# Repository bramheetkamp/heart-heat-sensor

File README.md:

# Pulse — Heart Rate + Core Temperature Wearable Companion

A consumer-grade iOS app and sync backend for a BLE wearable with a MAX30102 heart-rate sensor and dual temperature sensing, built on an nRF52840 DK running Nordic's `ble_app_hrs` firmware.

The hardware doesn't exist yet — everything works end-to-end against simulated data via **Demo Mode** so you can develop and demo now, then swap in the real device later.

---

## Branching

- **`develop`** is the **default / working branch** — branch your features off it and open PRs into it.
- **`main`** is the release branch (production-ready history).
- `develop` is protected: it can't be deleted or force-pushed. Day-to-day work happens on `develop`; merge into `main` for releases.

---

## Project layout

```
heart-heat-sensor/
├── ios/          iOS app (Swift + SwiftUI + CoreBluetooth)
└── backend/      Sync API (Node.js + TypeScript + Fastify + SQLite)
```

---

## 1. Running the backend

### Prerequisites
- Node.js ≥ 20
- (Optional) Docker + Docker Compose

### Quick start (Node.js)

```bash
cd backend
npm install
cp .env.example .env          # edit JWT_SECRET at minimum
npm run dev                   # starts on http://localhost:3100
```

### Quick start (Docker)

```bash
cd backend
docker-compose up
```

### Seed the database with demo data

```bash
npm run seed
```

This creates a test account (`test@example.com` / `password123`) preloaded with 35 days of readings across four scenarios and fires the warnings engine:

| Days    | Scenario                                    | Warnings fired          |
|---------|---------------------------------------------|-------------------------|
| 1–28    | Normal week with workouts and sleep         | None                    |
| 29–31   | Getting sick — creeping HR + temp baseline  | `GETTING_SICK`          |
| 32–33   | Overheating workout — temp spike to 39.1 °C | `OVERHEATING`           |
| 34–35   | Poor recovery — elevated HR, low HRV        | `FATIGUE_RECOVERY`      |

### Running backend tests

```bash
npm test
# 50 tests, all in-process via Fastify inject() — no port required
```

### API overview

| Method | Path | Auth | Description |
|--------|------|------|-------------|
| POST | `/auth/register` | — | Email + password registration |
| POST | `/auth/login` | — | Returns JWT |
| POST | `/auth/apple` | — | Sign in with Apple |
| POST | `/readings/batch` | JWT | Upload reading batch |
| GET  | `/readings` | JWT | Fetch history (`from`, `to`, `limit` params) |
| GET  | `/warnings` | JWT | Fetch user's warnings |
| GET  | `/warnings/:id` | JWT | Single warning detail |
| POST | `/warnings/recompute` | JWT | Re-run warnings engine |
| GET  | `/.well-known/apple-app-site-association` | — | Universal Links config |
| GET  | `/health` | — | Health check |

---

## 2. Running the iOS app

### Prerequisites

- macOS with **Xcode 15+** (iOS 17 SDK)
- [XcodeGen](https://github.com/yonaskolb/XcodeGen) (install via `brew install xcodegen`)

### Generate the Xcode project

```bash
cd ios
bash generate_project.sh    # installs XcodeGen if missing, then generates HeartRate.xcodeproj
open HeartRate.xcodeproj
```

Select any iPhone 17 Simulator and press **⌘R** to run.

> **Team ID**: open `project.yml`, find `DEVELOPMENT_TEAM: ""` and set your Apple Developer Team ID if you want to run on a physical device.

### Running iOS unit tests

```bash
cd ios
xcodebuild test \
  -project HeartRate.xcodeproj \
  -scheme HeartRate \
  -destination 'platform=iOS Simulator,name=iPhone 16' \
  2>&1 | xcpretty
```

Tests cover:
- `HRMeasurementParserTests` — HR characteristic byte parsing (8-bit, 16-bit, RR intervals, energy expended, sensor contact)
- `TemperatureMeasurementParserTests` — IEEE-11073 float decoding, Fahrenheit conversion, site hints
- `WarningsEngineTests` — all three warning rules, baseline computation, RMSSD calculation

---

## 3. Demo Mode

Demo Mode feeds **simulated data through the same BLE pipeline** as a real device — the UI, parsers, and warnings engine see no difference.

### Enabling Demo Mode

- **First launch**: tap *"I don't have my device yet — use demo mode"* during onboarding pairing step
- **Any time**: Settings → Demo Mode toggle
- The mode persists in `UserDefaults` key `isDemoMode`

### Scenario presets

| Scenario | What it simulates |
|----------|-------------------|
| **Normal Week** | Typical HR 55–75 bpm, core 36.4–36.8 °C, circadian rhythm, workouts |
| **Overheating Workout** | Core temp spike to 39.1 °C during an active session → fires `OVERHEATING` |
| **Getting Sick (3 days)** | Resting HR creeps up +3 bpm/day, core temp +0.15 °C/day → fires `GETTING_SICK` |
| **Poor Recovery** | Elevated resting HR + very regular RR intervals (near-zero HRV) → fires `FATIGUE_RECOVERY` |

Switch scenarios in **Settings → Demo Scenario** or via the wand button on the Dashboard. Switching seeds fresh readings and immediately re-runs the warnings engine.

---

## 4. Deep links

### Custom URL scheme (`heartrate://`)

| URL | Navigates to |
|-----|-------------|
| `heartrate://dashboard` | Dashboard |
| `heartrate://history/hr` | HR history chart |
| `heartrate://history/core` | Core temp chart |
| `heartrate://history/hrv` | HRV chart |
| `heartrate://warnings/<uuid>` | Warning detail |
| `heartrate://settings` | Settings |
| `heartrate://pair` | Device pairing |

### Testing in Simulator

```bash
# Open a deep link in the booted Simulator
xcrun simctl openurl booted "heartrate://dashboard"
xcrun simctl openurl booted "heartrate://warnings/123e4567-e89b-12d3-a456-426614174000"
xcrun simctl openurl booted "heartrate://history/core"
```

### Universal Links

The backend serves `/.well-known/apple-app-site-association`. To enable Universal Links in production:

1. Deploy the backend to `yourdomain.com` over HTTPS.
2. Edit `ios/HeartRate/HeartRate.entitlements` — replace `yourdomain.com` with your actual domain.
3. Set `APPLE_TEAM_ID` env var on the backend so the AASA file contains your real team ID.
4. Universal Links then work as `https://yourdomain.com/warnings/<id>` etc.

---

## 5. Testing BLE with a simulated peripheral (LightBlue)

If you have an iPhone/iPad with [LightBlue](https://punchthrough.com/lightblue/), you can advertise a fake HR sensor:

1. Open LightBlue → **Create Virtual Device**
2. Add service `180D` (Heart Rate)
3. Add characteristic `2A37` (HR Measurement)
   - Value example (72 bpm, no RR): `0x00 0x48`
   - Value example (65 bpm, two RR intervals): `0x10 0x41 0xAA 0x03 0xB8 0x03`
4. Set it to notify
5. Run the iOS app in Simulator on the **same Mac** (BLE works between phone and Simulator via the Mac's Bluetooth adapter)

For temperature, add service `1809`, characteristic `2A1C`:
- Example (36.7 °C): `0x00 0x6F 0x01 0x00 0xFF`

---

## 6. Wiring the iOS app to the real device

When the nRF52840 DK is ready:

1. Turn off Demo Mode in Settings
2. The app scans for peripherals advertising `0x180D` (Heart Rate Service)
3. On connect, it discovers and subscribes to `0x2A37` (HR) and `0x2A1C` (Temperature)
4. A second temperature characteristic on the same service is automatically detected and labelled "Site 2"

The firmware only needs to implement standard GATT: HR Measurement notify + Temperature Measurement notify.

---

## Architecture notes

### iOS

```
BLE Layer ──► BLEService ──► Parsers ──► DataStore (SwiftData)
                                              │
                                              ▼
                                       WarningsEngine
                                              │
                                              ▼
                                     Views / Dashboard
```

- **BLETransportProtocol** makes `CoreBluetoothTransport` and `MockBLETransport` interchangeable
- **WarningsEngine** is a pure struct with static methods — fully unit testable, no SwiftData dependency
- **AppRouter** uses `NavigationPath` + typed `AppRoute` enum — every screen is deep-linkable
- **SwiftData** persistence, **Swift Charts** for all trend charts
- Sync is additive and optional — the app works 100% offline

### Backend

- **Fastify** + **better-sqlite3** — fast to start, single binary for local dev
- **JWT** authentication, bcrypt password hashing
- Warnings engine runs server-side as a recompute operation; client engine handles offline/realtime
- SQLite WAL mode for concurrent reads during sync

### Extension point — Garmin Health API

The `SyncService.swift` contains a clearly marked stub:

```swift
// MARK: - Future: Garmin Health API Integration
// func syncGarminData(token: String) async throws { fatalError("Not implemented") }
```

On the backend, add a `/integrations/garmin` route group when ready.

---

## Environment variables (backend)

| Variable | Default | Description |
|----------|---------|-------------|
| `PORT` | `3100` | HTTP port |
| `JWT_SECRET` | `dev_secret_change_me` | **Change in production** |
| `DATABASE_PATH` | `./data/heartrate.db` | SQLite file path |
| `APPLE_CLIENT_ID` | `com.pulse.app` | Bundle ID checked against `aud` in Apple identity tokens |
| `APPLE_BUNDLE_ID` | `com.heartrate.app` | Bundle ID embedded in the AASA file |
| `APPLE_TEAM_ID` | `XXXXXXXXXX` | Apple Developer Team ID embedded in the AASA file |
| `API_BASE_URL` | `http://localhost:3100` | Set as Xcode env var to point the iOS app at staging |

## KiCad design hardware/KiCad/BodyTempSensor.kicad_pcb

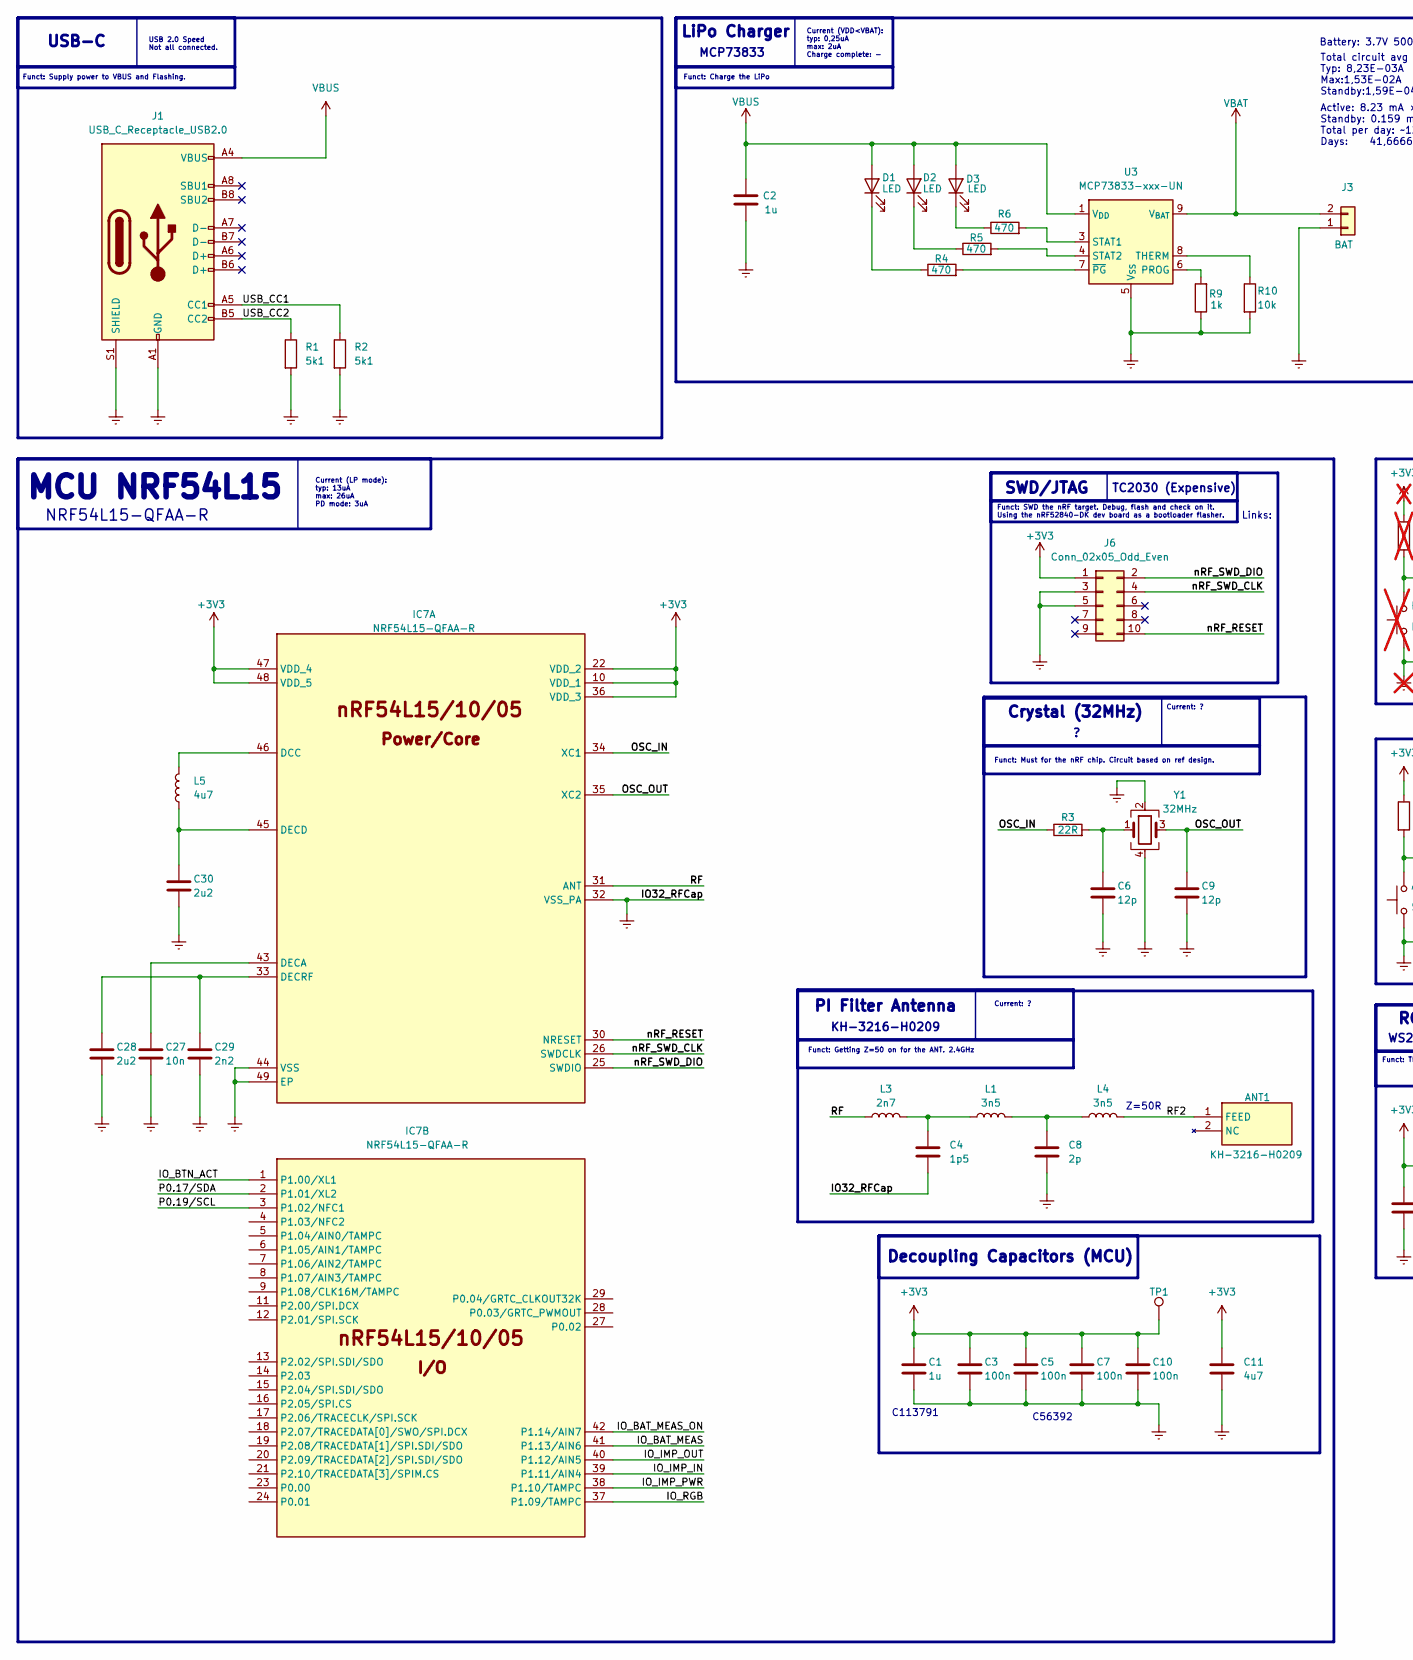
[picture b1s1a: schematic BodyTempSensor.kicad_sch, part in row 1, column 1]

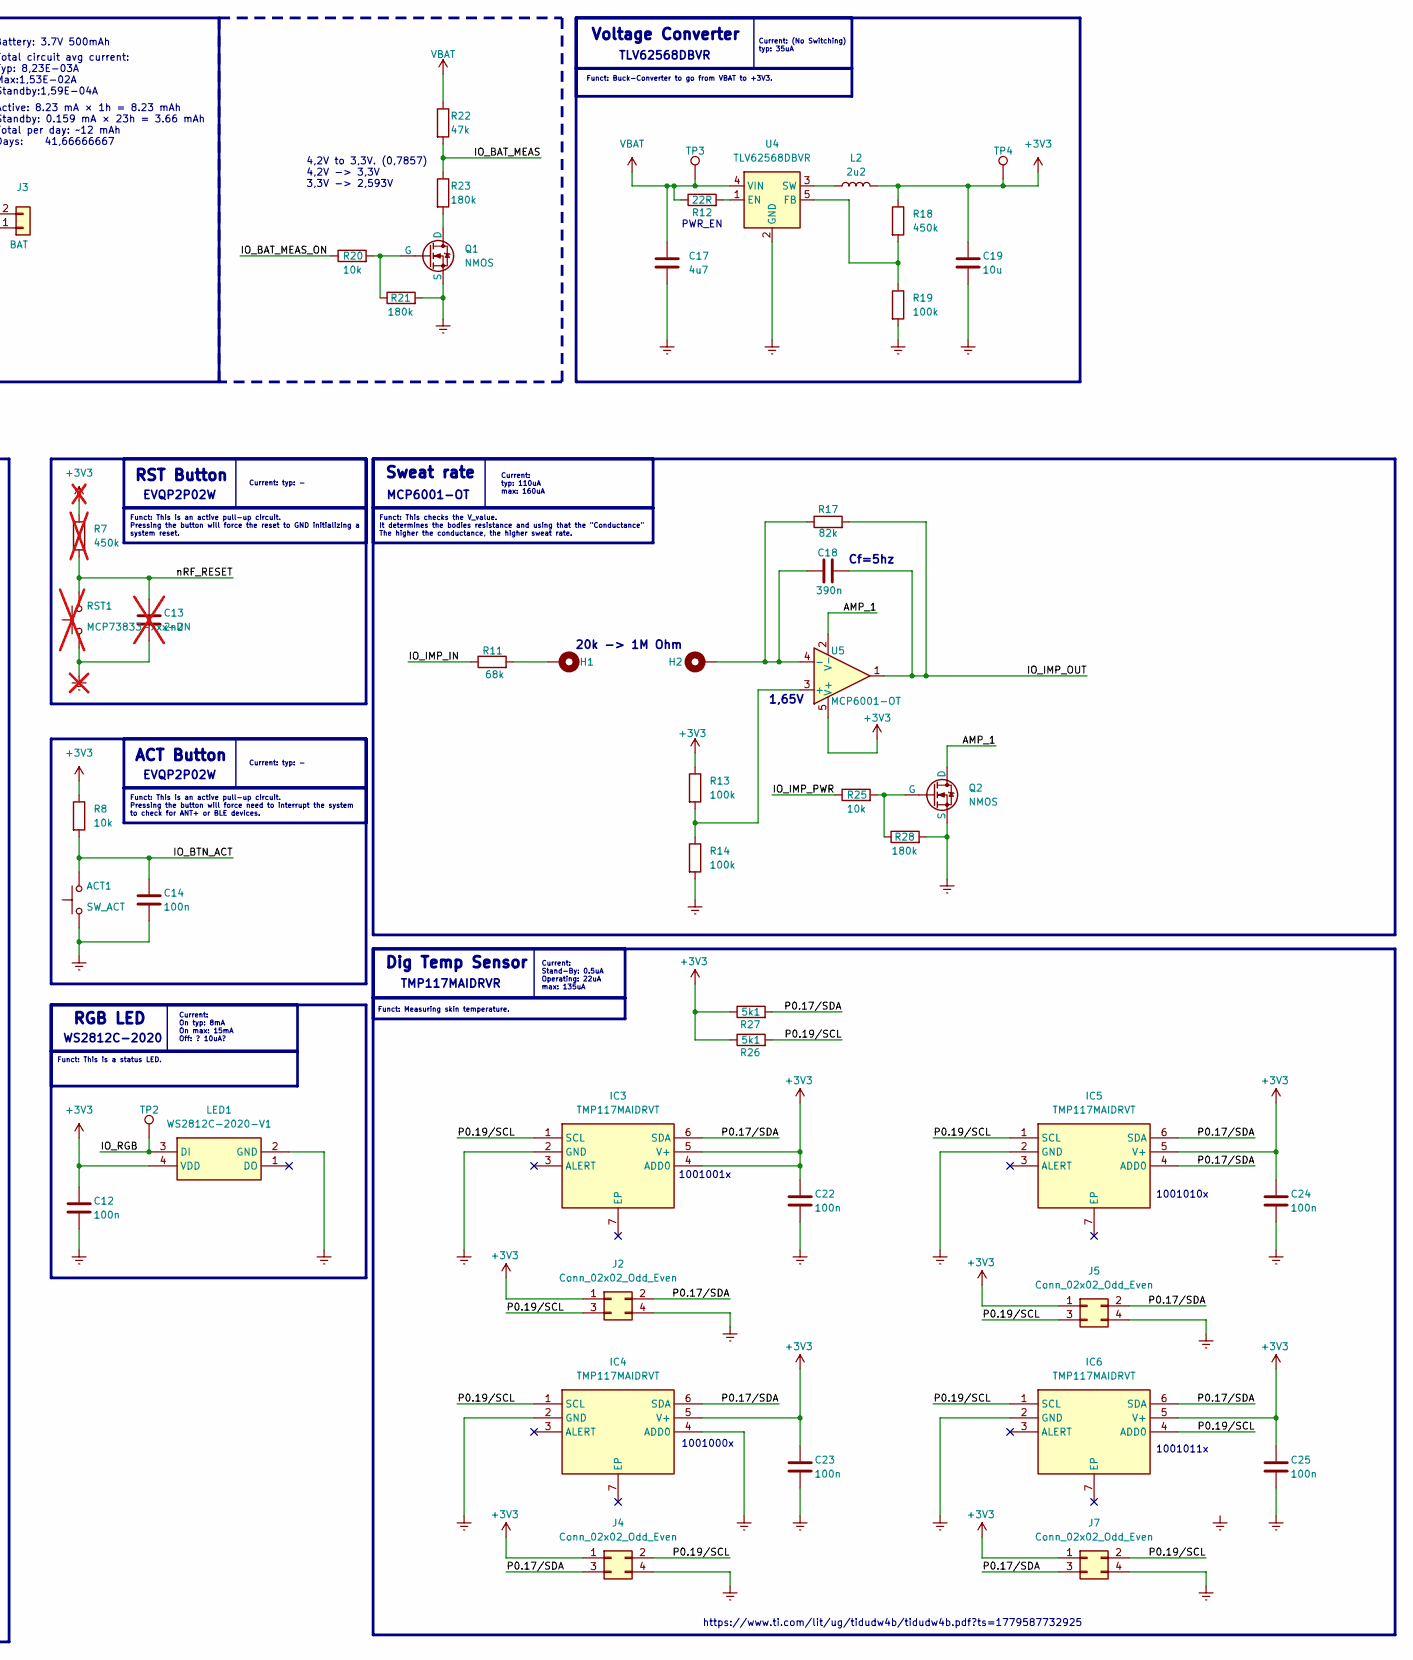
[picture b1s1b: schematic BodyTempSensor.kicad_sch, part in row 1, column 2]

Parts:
ACT1: SW_ACT; SW_SPST_EVQP2; Manufacturer_Part_Number EVQP2P02W; LCSC PART # C512395
ANT1: KH-3216-H0209; ANTC3216X140N; Manufacturer_Part_Number KH-3216-H0209; LCSC PART # C2925417
C1: 1u; C_0402_1005Metric_Pad0.74x0.62mm_HandSolder; Manufacturer_Part_Number CC0402MRX5R6BB105; LCSC PART # C113791
C2: 1u; C_0402_1005Metric_Pad0.74x0.62mm_HandSolder; Manufacturer_Part_Number CC0402KRX5R6BB105; LCSC PART # C106254
C3, C5, C7, C10, C12, C14, C22, C23, C24, C25: 100n; C_0402_1005Metric_Pad0.74x0.62mm_HandSolder; Manufacturer_Part_Number C1005X5R1E104KT000E; LCSC PART # C361203
C4: 1p5; C_0402_1005Metric_Pad0.74x0.62mm_HandSolder; LCSC PART # TBT
C6, C9: 12p; C_0402_1005Metric_Pad0.74x0.62mm_HandSolder; Manufacturer_Part_Number CC0402JRNPO9BN120; LCSC PART # C106201
C8: 2p; C_0402_1005Metric_Pad0.74x0.62mm_HandSolder; Manufacturer_Part_Number CC0402BRNPO9BN2R0; LCSC PART # CC0402BRNPO9BN2R0
C11, C17: 4u7; C_0402_1005Metric_Pad0.74x0.62mm_HandSolder; Manufacturer_Part_Number GRM155R60J475ME47D; LCSC PART # C82453
C13: 2n2; C_0402_1005Metric_Pad0.74x0.62mm_HandSolder; Manufacturer_Part_Number CC0402KRX7R9BB222; LCSC PART # C106861; not fitted
C18: 390n; C_0402_1005Metric_Pad0.74x0.62mm_HandSolder; Manufacturer_Part_Number TCC0402X5R394K160AT; LCSC PART # C7393858
C19: 10u; C_0402_1005Metric_Pad0.74x0.62mm_HandSolder; Manufacturer_Part_Number 0402X106M100CT; LCSC PART # C2992625
C27: 10n; C_0402_1005Metric_Pad0.74x0.62mm_HandSolder; Manufacturer_Part_Number CC0402KRX7R8BB103; LCSC PART # C327025
C28, C30: 2u2; C_0402_1005Metric_Pad0.74x0.62mm_HandSolder; Manufacturer_Part_Number 0402X225K100CT; LCSC PART # C295941
C29: 2n2; C_0402_1005Metric_Pad0.74x0.62mm_HandSolder; Manufacturer_Part_Number CC0402KRX7R9BB222; LCSC PART # C106861
D1, D2, D3: LED; LED_0402_1005Metric_Pad0.77x0.64mm_HandSolder; Manufacturer_Part_Number XL-1005SURC; LCSC PART # C965790
H1, H2: (no value)
IC3, IC4, IC5, IC6: TMP117MAIDRVT; SON65P200X200X80-7N; Manufacturer_Part_Number TMP117MAIDRVR; Mouser Part Number 595-TMP117MAIDRVT
IC7: NRF54L15-QFAA-R; QFN40P600X600X95-49N; Manufacturer_Part_Number NRF54L15-QFAA-R; Mouser Part Number 949-NRF54L15-QFAA-R
J1: USB_C_Receptacle_USB2.0; USB_C_Receptacle_GCT_USB4105-xx-A_16P_TopMnt_Horizontal; Manufacturer_Part_Number TYPE-C-31-M-14; LCSC PART # C223907
J2, J5: Conn_02x02_Odd_Even; PinHeader_2x02_P1.27mm_Vertical_SMD
J3: BAT; JST_PH_B2B-PH-K_1x02_P2.00mm_Vertical
J4, J7: Conn_02x02_Odd_Even; PinHeader_2x02_P1.27mm_Vertical
J6: Conn_02x05_Odd_Even; PinHeader_2x05_P1.27mm_Vertical
L1, L4: 3n5; L_0201_0603Metric_Pad0.64x0.40mm_HandSolder; Manufacturer_Part_Number TCGL0603C3N5SZT; LCSC PART # C52109755
L2: 2u2; L_Wurth_WE-LQSH-4020; Manufacturer_Part_Number SMNR4020-2.2UH; LCSC PART # C135262
L3: 2n7; L_0402_1005Metric_Pad0.77x0.64mm_HandSolder; Manufacturer_Part_Number LQG15HS2N7S02D; LCSC PART # C77108
L5: 4u7; L_0603_1608Metric_Pad1.05x0.95mm_HandSolder; Manufacturer_Part_Number MLZ1608M4R7WT000; LCSC PART # C76799
LED1: WS2812C-2020-V1; WS2812C2020; Manufacturer_Part_Number WS2812C-2020; LCSC PART # C2976072
Q1, Q2: NMOS; SOT-23; Manufacturer_Part_Number AO3400A; LCSC PART # C20917
R1, R2, R26, R27: 5k1; R_0402_1005Metric_Pad0.72x0.64mm_HandSolder; Manufacturer_Part_Number RC0402JR-075K1L; LCSC PART # C105873
R3, R12: 22R; R_0402_1005Metric_Pad0.72x0.64mm_HandSolder; Manufacturer_Part_Number ERJ2RKF22R0X; LCSC PART # C413049
R4, R5, R6: 470; R_0402_1005Metric_Pad0.72x0.64mm_HandSolder; Manufacturer_Part_Number SCR0603J470R; LCSC PART # C3017744
R7: 450k; R_0402_1005Metric_Pad0.72x0.64mm_HandSolder; Manufacturer_Part_Number FRC0402F4503TS; LCSC PART # C5159688; not fitted
R8, R10, R20, R25: 10k; R_0402_1005Metric_Pad0.72x0.64mm_HandSolder; Manufacturer_Part_Number WR04X1002FTL; LCSC PART # C163810
R9: 1k; R_0402_1005Metric_Pad0.72x0.64mm_HandSolder; Manufacturer_Part_Number RC0402FR-071KL; LCSC PART # C106235
R11: 68k; R_0402_1005Metric_Pad0.72x0.64mm_HandSolder; Manufacturer_Part_Number RC0402FR-0768KL; LCSC PART # C238338
R13, R14, R19: 100k; R_0402_1005Metric_Pad0.72x0.64mm_HandSolder; Manufacturer_Part_Number RT0402CRE07100KL; LCSC PART # C705662
R17: 82k; R_0402_1005Metric_Pad0.72x0.64mm_HandSolder; Manufacturer_Part_Number RC0402FR-0782KL; LCSC PART # C137932
R18: 450k; R_0402_1005Metric_Pad0.72x0.64mm_HandSolder; Manufacturer_Part_Number FRC0402F4503TS; LCSC PART # C5159688
R21, R23, R28: 180k; R_0402_1005Metric_Pad0.72x0.64mm_HandSolder; Manufacturer_Part_Number RC0402FR-07180KL; LCSC PART # C138046
R22: 47k; R_0402_1005Metric_Pad0.72x0.64mm_HandSolder; Manufacturer_Part_Number RC0402FR-0747KL; LCSC PART # C93943
RST1: MCP73833-xxx-UN; MSOP-10_3x3mm_P0.5mm; Manufacturer_Part_Number MCP73831T-2ACI/OT; LCSC PART # C424093; not fitted
TP1, TP2, TP3, TP4: TestPoint; TestPoint_Pad_D1.0mm
U3: MCP73833-xxx-UN; MSOP-10_3x3mm_P0.5mm; Manufacturer_Part_Number MCP73831T-2ACI/OT; LCSC PART # C424093
U4: TLV62568DBVR; SOT-23-5; Manufacturer_Part_Number TLV62568DBVR; LCSC PART # C163219
U5: MCP6001-OT; SOT-23-5; Manufacturer_Part_Number MCP6001T-I/OT; LCSC PART # C116490
Y1: 32MHz; Crystal_SMD_3225-4Pin_3.2x2.5mm; Manufacturer_Part_Number X322532MMB4SI; LCSC PART # C113671

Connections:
+3V3: C1.1, C3.1, C5.1, C7.1, C10.1, C11.1, C12.1, C19.1, C22.1, C23.1, C24.1, C25.1, IC3.4 (ADD0), IC3.5 (V+), IC4.5 (V+), IC5.5 (V+), IC6.5 (V+), IC7.10 (VDD_1), IC7.22 (VDD_2), IC7.36 (VDD_3), IC7.47 (VDD_4), IC7.48 (VDD_5), J2.1, J4.1, J5.1, J6.1, J7.1, L2.2, LED1.4 (VDD), R7.1, R8.1, R13.1, R18.1, R26.1, R27.1, TP1.1 (1_1), TP4.1 (1_1), U5.5 (V+)
/AMP_1: Q2.1 (D), U5.2 (V-)
/IO_BAT_MEAS: IC7.41 (P1.13/AIN6), R22.2, R23.1
/IO_BAT_MEAS_ON: IC7.42 (P1.14/AIN7), R20.1
/IO_BTN_ACT: ACT1.2, C14.1, IC7.1 (P1.00/XL1), R8.2
/IO_IMP_IN: IC7.39 (P1.11/AIN4), R11.1
/IO_IMP_OUT: C18.2, IC7.40 (P1.12/AIN5), R17.2, U5.1
/IO_IMP_PWR: IC7.38 (P1.10/TAMPC), R25.1
/IO_RGB: IC7.37 (P1.09/TAMPC), LED1.3 (DI), TP2.1 (1_1)
/OSC_IN: IC7.34 (XC1), R3.1
/OSC_OUT: C9.1, IC7.35 (XC2), Y1.3
/P0.17/SDA: IC3.6 (SDA), IC4.6 (SDA), IC5.4 (ADD0), IC5.6 (SDA), IC6.6 (SDA), IC7.2 (P1.01/XL2), J2.2, J4.3, J5.2, J7.3, R27.2
/P0.19/SCL: IC3.1 (SCL), IC4.1 (SCL), IC5.1 (SCL), IC6.1 (SCL), IC6.4 (ADD0), IC7.3 (P1.02/NFC1), J2.3, J4.2, J5.3, J7.2, R26.2
/RF: IC7.31 (ANT), L3.1
/RF2: ANT1.1 (FEED_1), L4.2
/USB_CC1: J1.A5 (CC1), R2.1
/USB_CC2: J1.B5 (CC2), R1.1
/nRF_RESET: C13.1, IC7.30 (NRESET), J6.10, R7.2, RST1.2
/nRF_SWD_CLK: IC7.26 (SWDCLK), J6.4
/nRF_SWD_DIO: IC7.25 (SWDIO), J6.2
Earth: ACT1.1, C1.2, C2.1, C3.2, C4.2, C5.2, C6.2, C7.2, C8.2, C9.2, C10.2, C11.2, C12.2, C13.2, C14.2, C17.2, C19.2, C22.2, C23.2, C24.2, C25.2, C27.2, C28.2, C29.2, C30.2, IC3.2 (GND), IC4.2 (GND), IC4.4 (ADD0), IC5.2 (GND), IC6.2 (GND), IC7.32 (VSS_PA), IC7.44 (VSS), IC7.49 (EP), J1.A1 (GND), J1.A12 (GND), J1.B1 (GND), J1.B12 (GND), J1.S1 (SHIELD), J2.4, J3.1, J4.4, J5.4, J6.3, J6.5, J7.4, LED1.2 (GND), Q1.3 (S), Q2.3 (S), R1.2, R2.2, R9.1, R10.2, R14.2, R19.2, R21.2, R28.2, RST1.1, U3.5 (V_{SS}), U4.2 (GND), Y1.2, Y1.4
unnamed: C4.1, L1.1, L3.2
unnamed: C6.1, R3.2, Y1.1
unnamed: C8.1, L1.2, L4.1
unnamed: D1.1 (K), R4.1
unnamed: D2.1 (K), R5.1
unnamed: D3.1 (K), R6.1
unnamed: H1.1 (1_1), R11.2
unnamed: IC7.46 (DCC), L5.2
unnamed: C27.1, IC7.43 (DECA)
unnamed: C30.1, IC7.45 (DECD), L5.1
unnamed: C28.1, C29.1, IC7.33 (DECRF)
unnamed: Q1.1 (D), R23.2
unnamed: Q1.2 (G), R20.2, R21.1
unnamed: Q2.2 (G), R25.2, R28.1
unnamed: R9.2, U3.6 (PROG)
unnamed: R6.2, U3.3 (STAT1)
unnamed: R5.2, U3.4 (STAT2)
unnamed: R10.1, U3.8 (THERM)
unnamed: R4.2, U3.7 (~PG)
unnamed: R12.2, U4.1 (EN)
unnamed: R18.2, R19.1, U4.5 (FB)
unnamed: L2.1, U4.3 (SW)
unnamed: R13.2, R14.1, U5.3 (+)
unnamed: C18.1, H2.1 (1_1), R17.1, U5.4 (-)
VBAT: C17.1, J3.2, R12.1, R22.1, TP3.1 (1_1), U3.9 (V_{BAT}), U3.10 (V_{BAT}), U4.4 (VIN)
VBUS: C2.2, D1.2 (A), D2.2 (A), D3.2 (A), J1.A4 (VBUS), J1.A9 (VBUS), J1.B4 (VBUS), J1.B9 (VBUS), U3.1 (V_{DD}), U3.2 (V_{DD})

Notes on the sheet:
https://www.ti.com/lit/ug/tidudw4b/tidudw4b.pdf?ts=1779587732925
NRF54L15-QFAA-R
EVQP2P02W
Funct: Must for the nRF chip. Circuit based on ref design.
Crystal (32MHz)
Funct: Supply power to VBUS and Flashing.
MCP73833
Current: ?
Funct: Measuring skin temperature.
Active: 8.23 mA × 1h = 8.23 mAh Standby: 0.159 mA × 23h = 3.66 mAh Total per day: ~12 mAh Days: 41,66666667
Funct: Buck-Converter to go from VBAT to +3V3.
1,65V
Current: typ: -
Sweat rate
TLV62568DBVR
RGB LED
MCP6001-OT
Current (LP mode): typ: 13uA max: 26uA PD mode: 3uA
Current: typ: 110uA max: 160uA
Current (VDD<VBAT): typ: 0,25uA max: 2uA Charge complete: -
20k -> 1M Ohm
Funct: This is an active pull-up circuit. Pressing the button will force need to interrupt the system to check for ANT+ or BLE devices.
Z=50R
C113791
TMP117MAIDRVR
C56392
Funct: SWD the nRF target. Debug, flash and check on it. Using the nRF52840-DK dev board as a bootloader flasher.
Battery: 3.7V 500mAh
Funct: Getting Z=50 on for the ANT. 2.4GHz
Funct: This is a status LED.
Voltage Converter
ACT Button
PI Filter Antenna
Current: On typ: 8mA On max: 15mA Off: ? 10uA?
LiPo Charger
Total circuit avg current: Typ: 8,23E-03A Max:1,53E-02A Standby:1,59E-04A
TC2030 (Expensive)
Decoupling Capacitors (MCU)
USB 2.0 Speed Not all connected.
SWD/JTAG

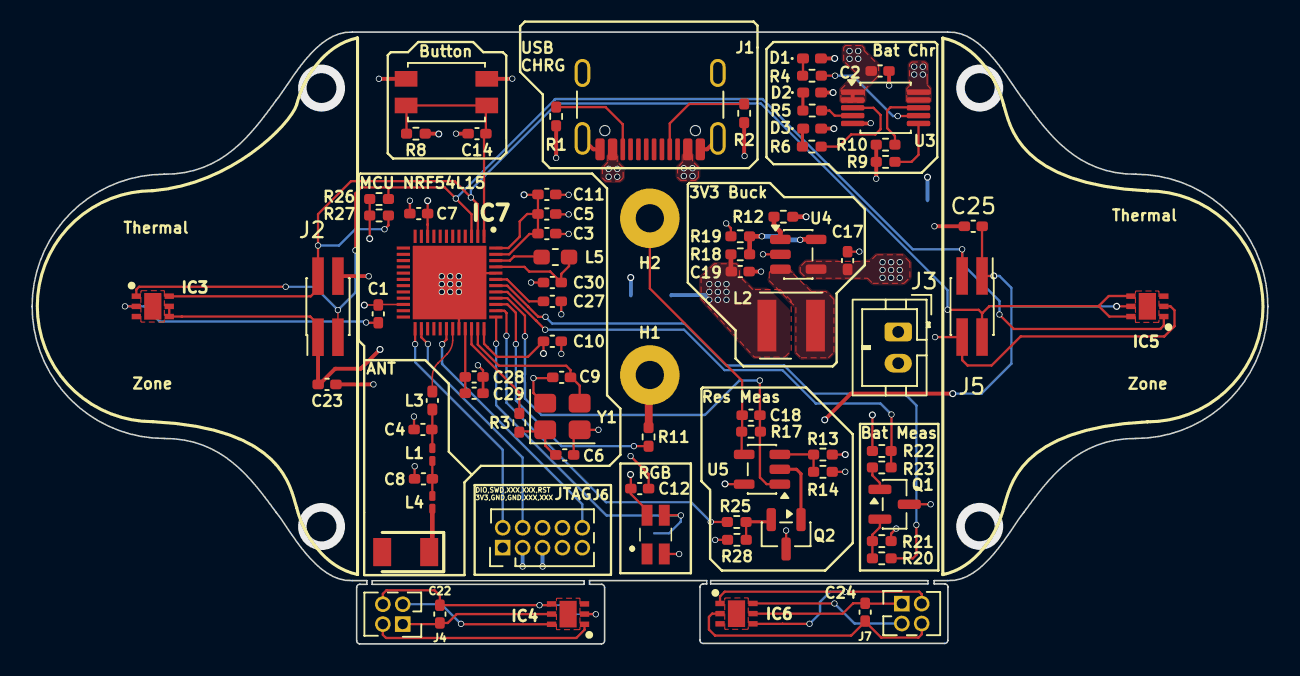
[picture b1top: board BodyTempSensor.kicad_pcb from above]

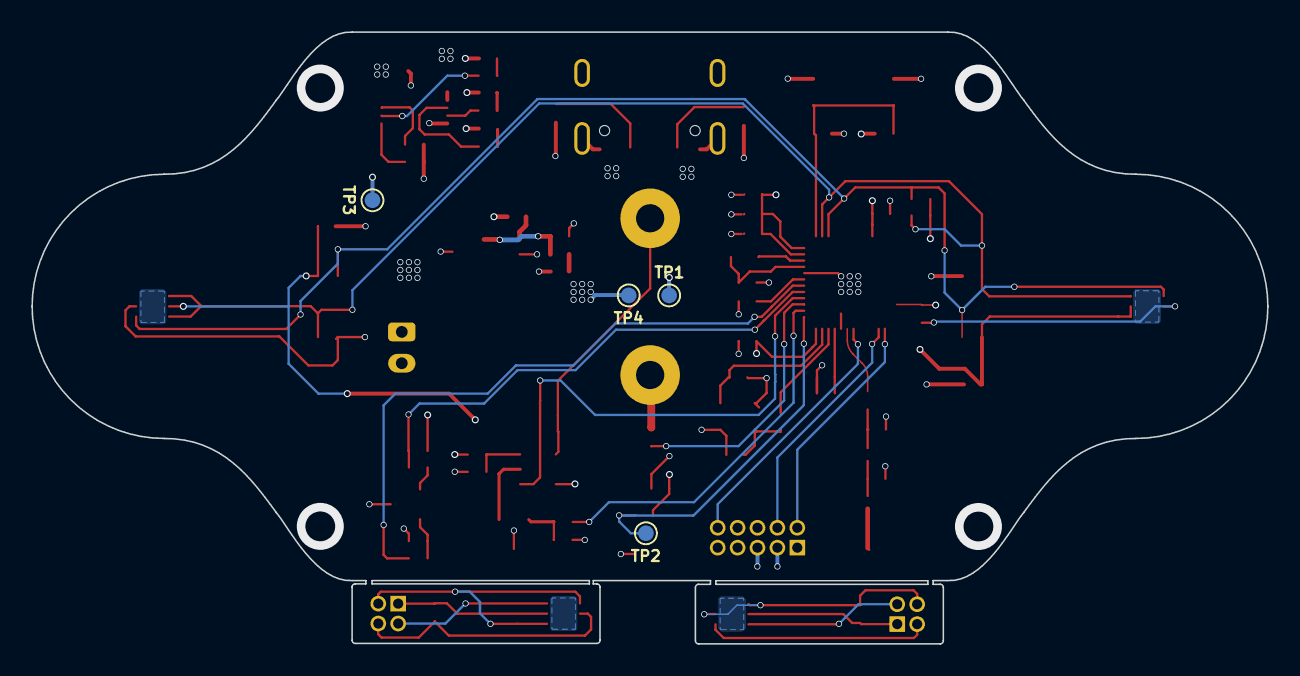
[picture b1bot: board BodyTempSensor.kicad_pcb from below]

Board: 4 copper layers, 78.9 x 39.0 mm, 83 parts (4 on the bottom side), 47 nets.

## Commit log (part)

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2026-06-12 feat: add Pulse iOS app + backend — complete initial implementation
    Backend (Node/TypeScript/Fastify/SQLite):
    - Auth routes: email+password register/login, Sign in with Apple stub
    - Readings batch upload + paginated history fetch
    - Warnings engine: OVERHEATING, GETTING_SICK, FATIGUE_RECOVERY rules
    - /.well-known/apple-app-site-association for Universal Links
    - Seed script: 35 days of realistic data across 4 scenarios
2026-06-12 docs: add ROADMAP.md and IMPROVEMENT_LOG.md
    Baseline audit of the initial implementation:
    - All 19 backend tests pass.
    - Seed fires 2/3 warnings; OVERHEATING blocked by 24 h engine window
    (seed data is 37 h old). Fix tracked in ROADMAP.
    - ROADMAP lists all capability checklist items from the product spec
    with current checked/unchecked status.
2026-06-12 fix(engine): extend OVERHEATING window 24 h → 48 h; add engine unit tests
    The overheating check filtered to readings from the last 24 hours, but the
    seed data places the overheating workout 37–38 hours in the past (day 32 at
    hour 10/11, dayOffset = 2 days). The narrower window caused OVERHEATING
    never to fire from the seed script.
    Changes:
    - warningsEngine.ts: bump OVERHEATING lookback from 24 h to 48 h. A 48-hour
2026-06-12 docs: update ROADMAP and IMPROVEMENT_LOG for festive-bell work
    Documents OVERHEATING fix and new engine unit tests built on
    claude/festive-bell-a9ari0 (pending merge). Updates next-run instructions
    with recommended order: rate limiting → Apple JWKS verification → iOS review.
    https://claude.ai/code/session_01GxK9phAquek6CZJHbMa1sA
2026-06-12 feat(backend): add rate limiting on auth and readings endpoints
    - Register @fastify/rate-limit v9 globally (200 req/min backstop)
    - /auth/register: 5 req / 15 min per IP (brute-force / spam protection)
    - /auth/login, /auth/apple: 10 req / 15 min per IP
    - /readings/batch: 100 req / min per IP (secondary layer; JWT is primary)
    - All limits configurable via BuildServerOptions (authRateLimit / readingsRateLimit)
    so tests can pass tight values without touching production defaults
2026-06-12 docs: update ROADMAP and IMPROVEMENT_LOG after festive-bell merge and rate-limiting build
    - Mark OVERHEATING window fix, engine unit tests, seed warnings as complete
    - Mark rate limiting as complete (on claude/work-rate-limiting, pending review)
    - Update backend test count: 40/40
    - Next-run instructions: review rate-limiting branch, then Apple JWKS verification
    https://claude.ai/code/session_01S8UrkrNbWY9omasDAbwLKr
2026-06-13 feat(backend): verify Apple identity token against JWKS (RS256, iss, aud, exp)
    Replace stub base64-decode with real JOSE signature verification:
    - New service `appleAuth.ts`: `verifyAppleToken` (RS256 via JWTVerifyGetKey),
    `makeAppleJWKS` (live Apple endpoint, lazy), `makeLocalJWKS` (test helper)
    - `BuildServerOptions.appleJwks` + `.appleAudience` allow JWKS injection in tests
    - `fastify.appleJwks` / `fastify.appleAudience` decorators accessible from routes
    - `APPLE_CLIENT_ID` env var documented in `.env.example`
2026-06-13 docs: update ROADMAP and IMPROVEMENT_LOG after rate-limiting merge and apple-jwks build
    - ROADMAP: check Apple Sign-In JWKS item; update test count to 50/50
    - LOG: record rate-limiting merge, apple-jwks branch work, next run instructions
    https://claude.ai/code/session_019FpWP8TgS1YUBMvE3ABs3W
2026-06-13 fix(ios): correct ParseError scope and fatigue threshold units in tests; verify all quality gates
    - HRMeasurementParserTests: ParseError is module-scoped, not nested in
    HRMeasurementParser — fix two occurrences of HRMeasurementParser.ParseError.tooShort
    (definite compile error in Xcode)
    - WarningsEngineTests: fatigueHRThreshold and fatigueHRVThreshold are ratios
    (0.08 = 8%, 0.80 = 80%), not percentages — test was setting 8.0 and 80.0
    which made the fatigue warning unreachable
2026-06-13 docs: update IMPROVEMENT_LOG after apple-jwks merge and final quality gates build
    https://claude.ai/code/session_01UwMcu193u2p3wKnNf5xyop
2026-06-13 docs: PROJECT COMPLETE — final audit passed, develop merged to main
    50/50 backend tests passing, seed fires all 3 warnings, all quality gates
    checked. iOS test fixes (ParseError scope, fatigue ratios) merged. Roadmap
    marked finished.
    https://claude.ai/code/session_01BoFz1ChuY2nRe7cToSfu54
2026-06-14 chore: sync docs from develop — PROJECT COMPLETE state
    Bring ROADMAP.md and IMPROVEMENT_LOG.md onto this branch to match
    origin/develop. These files were read during orientation; committing
    them satisfies the stop-hook requirement to leave no uncommitted state.
    https://claude.ai/code/session_01F3tyTMNqx5D8g7LfX7xTQC
2026-06-14 docs: record 2026-06-14 orientation run — iOS improvements merged into develop
    develop was behind main by 8 post-PROJECT COMPLETE commits (iOS runtime fixes,
    dark mode, pairing flow, notifications). Merged claude/festive-bell-up9kmf to
    bring develop in sync. Backend 50/50 tests passing.
    https://claude.ai/code/session_016hGR2nvV6XzVjPLJ4k3sm4
2026-06-15 docs: record 2026-06-15 run — BodyTempSensor + EDA features documented, develop → main sync
    - ROADMAP.md: add new items for BodyTempSensor BLE profile, BodyTempFrameParser,
    EDA metric (dashboard/history/sync/migration), BLE_CONTRACT.md, reliability fixes,
    sync upload contract fix, 180-day retention prune; update test count to 54/54;
    correct PROJECT COMPLETE date to 2026-06-15
    - IMPROVEMENT_LOG.md: add entry documenting fbdf55f (BodyTempSensor + EDA commit
    pushed to main by prior session), verification results, Linux caveats
2026-06-15 docs: record 2026-06-15 orientation run — Foundation Models verified, develop → main synced
    https://claude.ai/code/session_019fMNA7jeAuGkzcRCTHiRcs
2026-06-17 docs: record 2026-06-17 run — personalized onboarding, streak card, character voices merged
2026-06-17 feat(ios): customizable dashboard — DashboardLayoutService, CustomizeDashboardView, section-aware DashboardView
2026-06-17 feat: streak milestone notifications, character unlocks, and history daily averages
    - NotificationService: fires banner at 7/14/30/60/90/180-day streak milestones;
    Hoot (7d) and Ember (30d) get character-unlock messages; tapping unlock banners
    deep-links to Settings. Schedules a recurring Sunday 9 AM weekly digest on
    first notification grant.
    - DashboardView: calls checkAndNotifyStreak(days:character:) in every refresh so
    milestones are caught as soon as streak data updates.
2026-06-17 feat: CSV data export in Settings + character-voiced warning tips
    - SettingsView: new "Export Data as CSV" button in About section that presents
    ExportDataView — a sheet that queries all readings, generates a temp .csv file
    (timestamp, HR, core/skin temp, HRV, EDA, activity), and offers it via
    SwiftUI ShareLink so users can save to Files, AirDrop, or email it.
    - WarningDetailView: adds a character mascot quote at the top of the
    "What you can do" card — the selected companion speaks in their voice about
2026-06-17 feat: sleep demo data, 24h sleep window, confetti on excellent recovery, haptic feedback
    - DemoModeService: 8 sleep readings per night (22:00-06:30, every ~90 min)
    with per-activity HR ranges (sleep: 52-62, rest: 62-72, active: 95-130).
    Future timestamps filtered so seeded data never includes readings that
    haven't happened yet. PoorRecovery scenario shows elevated sleep HR (62-72)
    to represent suppressed recovery even overnight.
    - SleepQualityCard: extended lookback from 16h to 24h so last night's data
2026-06-18 feat: Add lock files for BodyTempSensor project in KiCad
    - Created lock file for PCB design: ~BodyTempSensor.kicad_pcb.lck
    - Created lock file for schematic design: ~BodyTempSensor.kicad_sch.lck
2026-06-18 feat: Add BLE service and sensor modules for biometric data collection
    - Introduced `ble_service.h` and `ble_service.c` to manage BLE GATT service for biometric data transmission.
    - Implemented `eda_gsr.c` and `eda_gsr.h` for electrodermal activity (GSR) sensing, including ADC setup and sampling.
    - Added `heatflux.c` and `heatflux.h` to estimate core temperature using dual TMP117 sensors based on heat flux principles.
    - Created `temp_tmp117.c` and `temp_tmp117.h` to manage TMP117 temperature sensors, including initialization and reading.
    - Developed `battery.c` and `battery.h` to decode MCP73833 charge status, with optional GPIO handling based on devicetree configuration.
    - Centralized loggi
2026-06-22 Updated KiCad and BOM
2026-06-22 Small edit on the PCB ANT
